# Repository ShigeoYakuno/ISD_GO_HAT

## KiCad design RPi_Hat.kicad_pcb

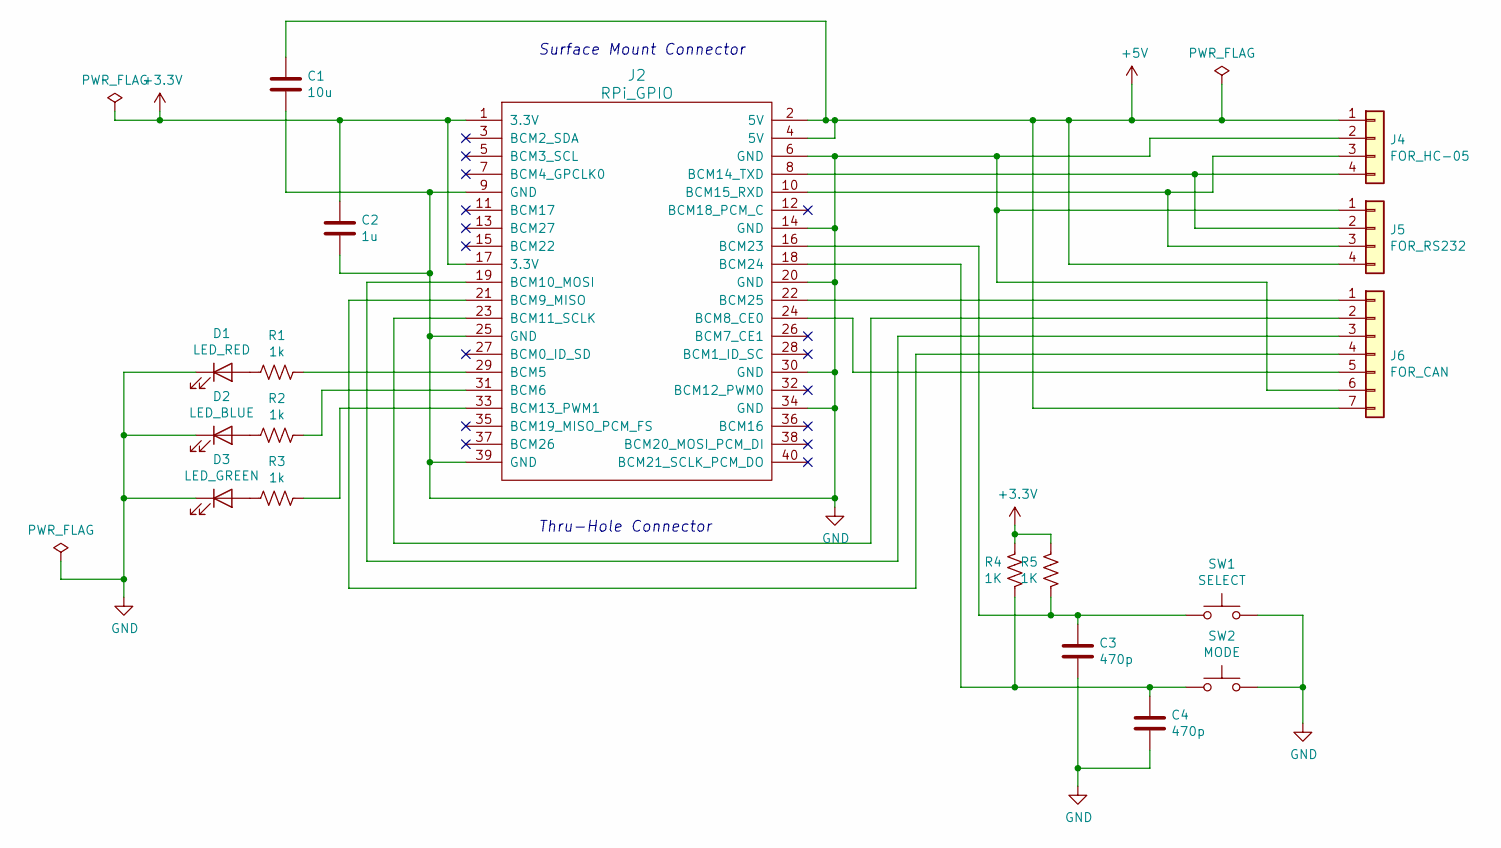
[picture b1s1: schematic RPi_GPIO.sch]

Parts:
C1: 10u; C_0805_2012Metric_Pad1.18x1.45mm_HandSolder
C2: 1u; C_0805_2012Metric_Pad1.18x1.45mm_HandSolder
C3, C4: 470p; C_0603_1608Metric_Pad1.08x0.95mm_HandSolder
D1: LED_RED; D_0603_1608Metric_Pad1.05x0.95mm_HandSolder
D2: LED_BLUE; D_0603_1608Metric_Pad1.05x0.95mm_HandSolder
D3: LED_GREEN; D_0603_1608Metric_Pad1.05x0.95mm_HandSolder
J2: RPi_GPIO; Pin_Header_Straight_2x20
J4: FOR_HC-05; PinHeader_1x04_P2.54mm_Vertical
J5: FOR_RS232; PinHeader_1x04_P2.54mm_Vertical
J6: FOR_CAN; PinHeader_1x07_P2.54mm_Vertical
R1, R2, R3: 1k; R_0603_1608Metric_Pad0.98x0.95mm_HandSolder
R4, R5: 1K; R_0603_1608Metric_Pad0.98x0.95mm_HandSolder
SW1: SELECT; Switch_Tactile_SMD_6x6mm
SW2: MODE; Switch_Tactile_SMD_6x6mm

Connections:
+3V3: C2.1, J2.1 (3.3V), J2.17 (3.3V), R4.2, R5.2
+5V: C1.1, J2.2 (5V), J2.4 (5V), J4.1, J5.4, J6.7
GND: C1.2, C2.2, C3.2, C4.2, D1.1 (K), D2.1 (K), D3.1 (K), J2.6 (GND), J2.9 (GND), J2.14 (GND), J2.20 (GND), J2.25 (GND), J2.30 (GND), J2.34 (GND), J2.39 (GND), J4.2, J5.1, J6.6, SW1.2, SW2.2
unnamed: C3.1, J2.16 (BCM23), R5.1, SW1.1
unnamed: C4.1, J2.18 (BCM24), R4.1, SW2.1
unnamed: D1.2 (A), R1.1
unnamed: D2.2 (A), R2.1
unnamed: D3.2 (A), R3.1
unnamed: J2.8 (BCM14_TXD), J4.4, J5.2
unnamed: J2.10 (BCM15_RXD), J4.3, J5.3
unnamed: J2.19 (BCM10_MOSI), J6.3
unnamed: J2.21 (BCM9_MISO), J6.4
unnamed: J2.22 (BCM25), J6.1
unnamed: J2.23 (BCM11_SCLK), J6.2
unnamed: J2.24 (BCM8_CE0), J6.5
unnamed: J2.29 (BCM5), R1.2
unnamed: J2.31 (BCM6), R2.2
unnamed: J2.33 (BCM13_PWM1), R3.2

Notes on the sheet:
Surface Mount Connector
Thru-Hole Connector

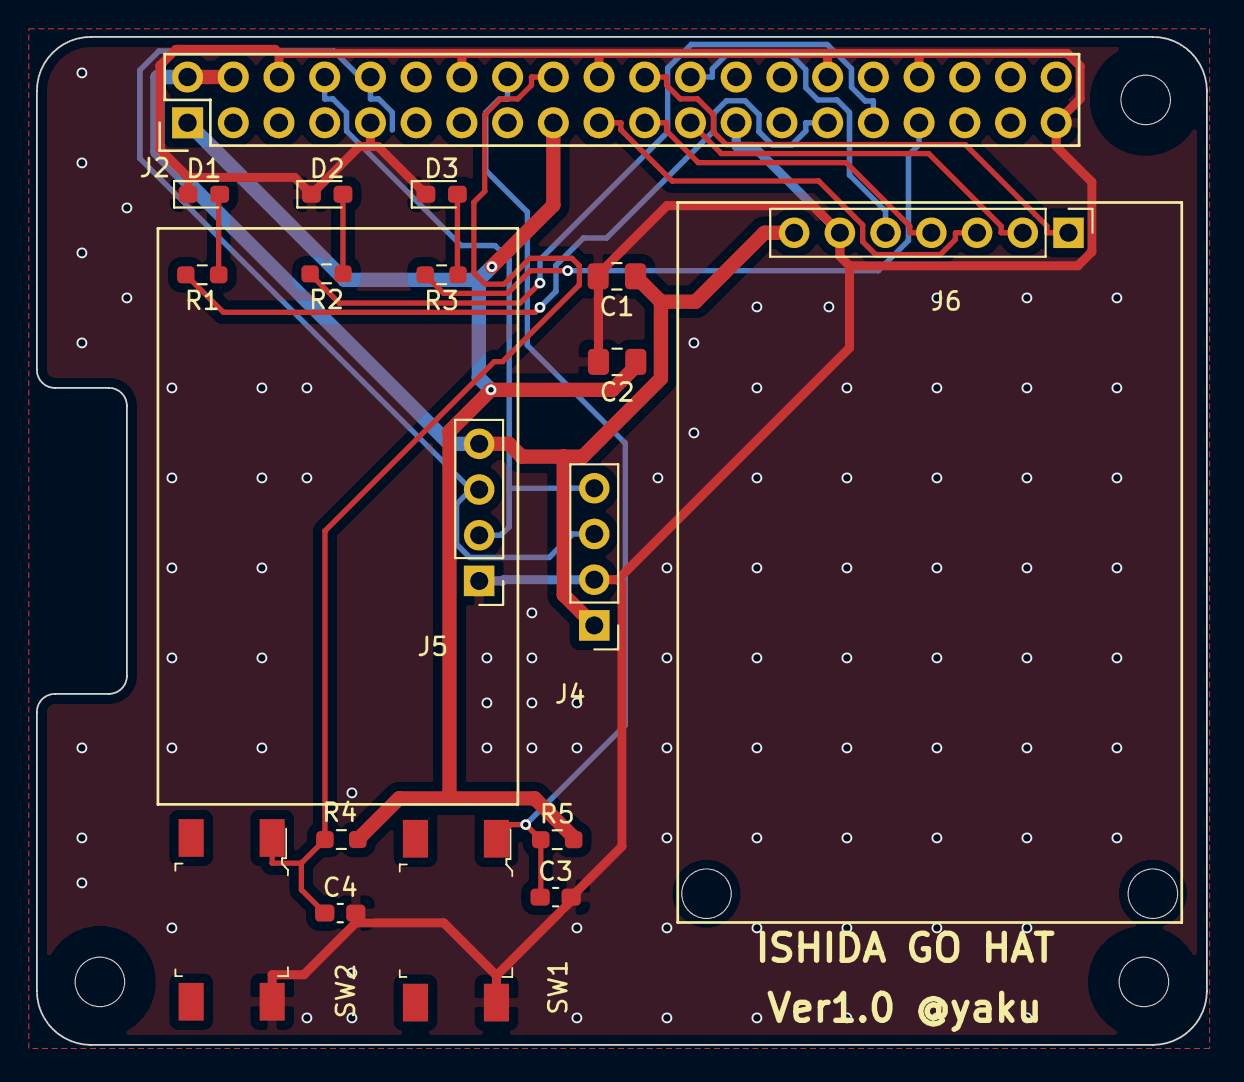
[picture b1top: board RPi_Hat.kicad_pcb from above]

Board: 2 copper layers, 65.0 x 56.0 mm, 23 parts (0 on the bottom side), 18 nets.

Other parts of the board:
pad2: pad2; RPi_Hat_Mounting_Hole
pad3: pad3; RPi_Hat_Mounting_Hole
pad4: pad4; RPi_Hat_Mounting_Hole
pad5: pad5; RPi_Hat_Mounting_Hole
pad6: pad6; RPi_Hat_Mounting_Hole

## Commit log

2023-12-18 ver1.0
